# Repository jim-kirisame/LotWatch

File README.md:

# LotWatch

LotWatch是一个自制的蓝牙手表项目。它使用了nRF51822作为核心，mma8452为加速度计。

使用[nRF SDK V10.0](https://developer.nordicsemi.com/nRF5_SDK/nRF51_SDK_v10.x.x/nRF51_SDK_10.0.0_dc26b5e.zip)开发，并在Keil MDK v5下编译通过。

## 文件结构

- app-js：手机端应用程序，使用Cordova编写
- Application：手表的主程序部分
- Bootloader：手表的Bootloader，用于OTA
- Hardware：硬件设计
- Release：编译好的各个程序，可以直接使用。

其余事项见各文件夹下的说明。

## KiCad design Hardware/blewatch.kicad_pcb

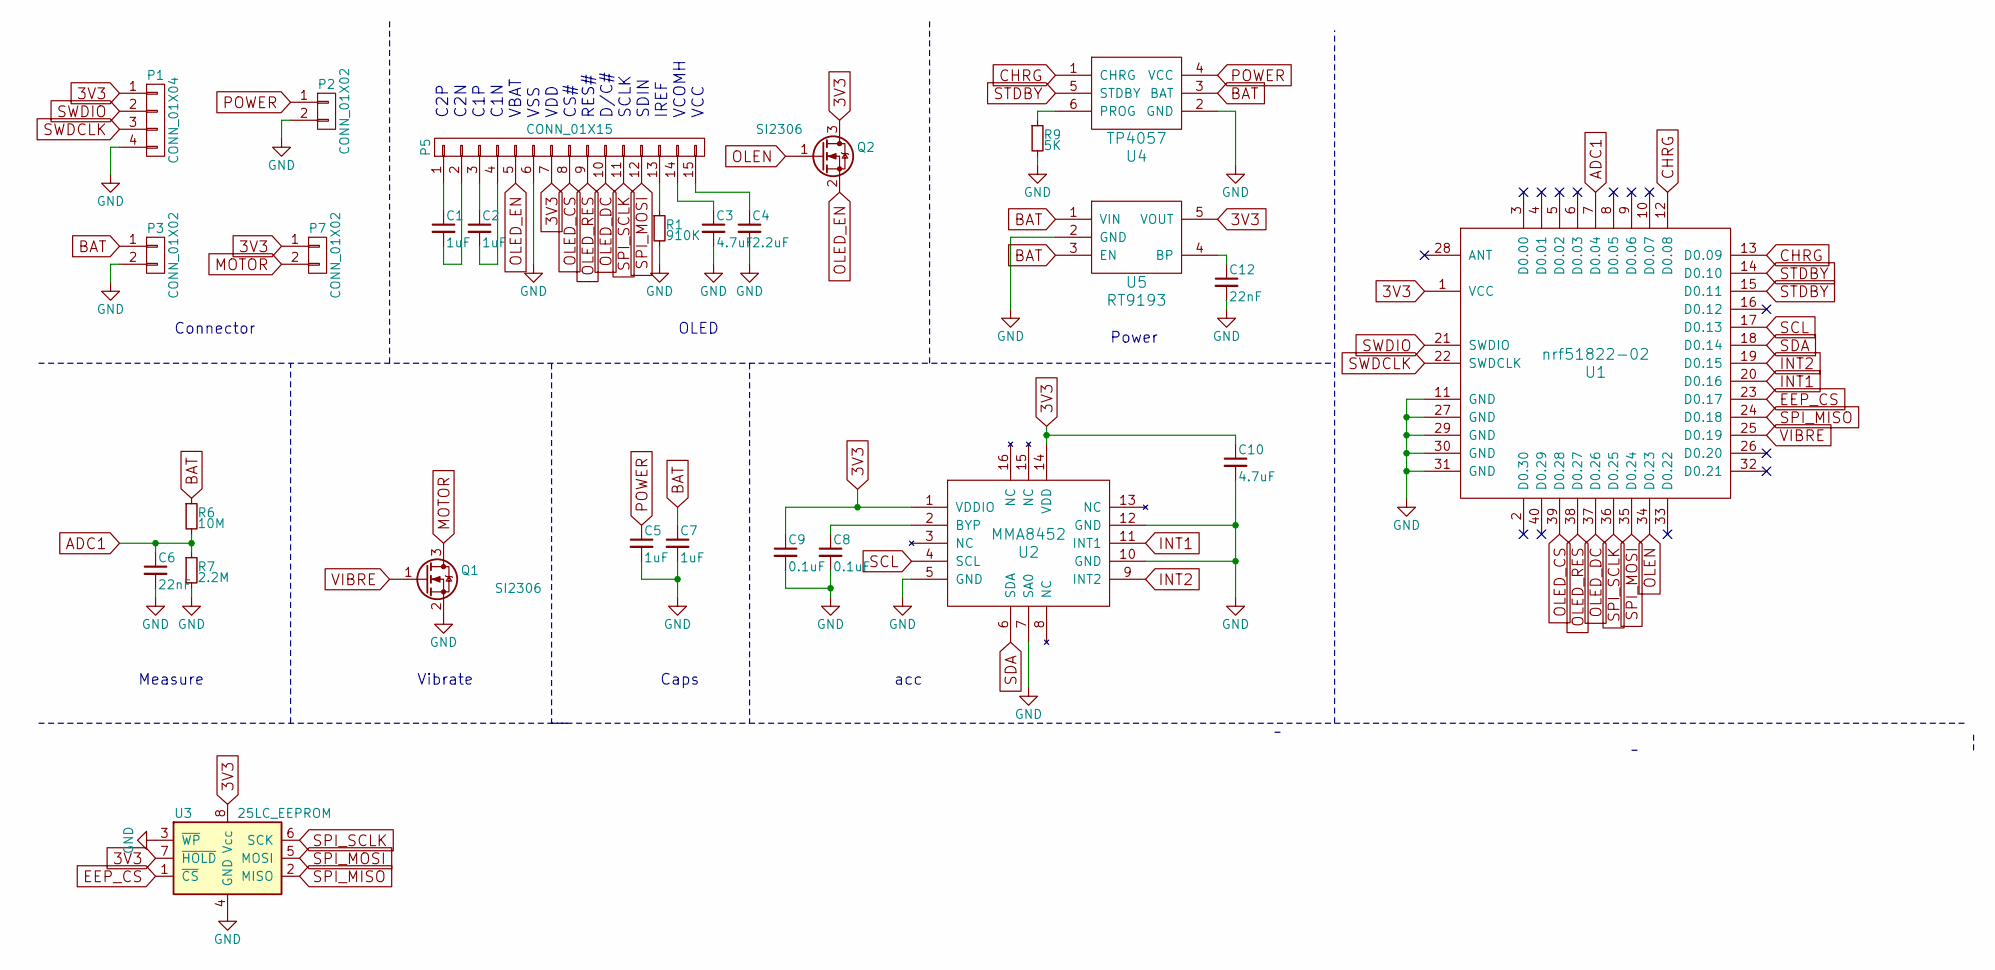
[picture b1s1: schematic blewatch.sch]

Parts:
C1, C2, C5, C7: 1uF; C_0805
C3, C10: 4.7uF; C_0805
C4: 2.2uF; C_0805
C6, C12: 22nF; C_0805
C8, C9: 0.1uF; C_0805
P1: CONN_01X04; SIP-4-1.27
P2, P3, P7: CONN_01X02; SIP-2-1.27
P5: CONN_01X15; OLED-15PIN
Q1, Q2: SI2306; SOT-23
R1: 910K; R_0805
R6: 10M; R_0805
R7: 2.2M; R_0805
R9: 5K; R_0805
U1: nrf51822-02; nRF51822-02
U2: MMA8452; QFN-16-1EP_3x3mm_Pitch0.5mm_SPEC
U3: 25LC_EEPROM; SOIC-8-N
U4: TP4057; SOT-23-6
U5: RT9193; SOT-23-5

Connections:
3V3: C9.1, C10.1, P1.1, P5.7, P7.1, Q2.3 (D), U1.1 (VCC), U2.1 (VDDIO), U2.14 (VDD), U3.7 (~HOLD), U3.8 (Vcc), U5.5 (VOUT)
ADC1: C6.1, R6.2, R7.1, U1.7 (D0.04)
BAT: C7.1, P3.1, R6.1, U4.3 (BAT), U5.1 (VIN), U5.3 (EN)
CHRG: U1.12 (D0.08), U1.13 (D0.09), U4.1 (CHRG)
EEP_CS: U1.23 (D0.17), U3.1 (~CS)
GND: C3.2, C4.2, C5.2, C6.2, C7.2, C8.2, C9.2, C10.2, C12.2, P1.4, P2.2, P3.2, P5.6, Q1.2 (S), R1.2, R7.2, R9.2, U1.11 (GND), U1.27 (GND), U1.29 (GND), U1.30 (GND), U1.31 (GND), U2.5 (GND), U2.7 (SA0), U2.10 (GND), U2.12 (GND), U3.3 (~WP), U3.4 (GND), U4.2 (GND), U5.2 (GND)
INT1: U1.20 (D0.16), U2.11 (INT1)
INT2: U1.19 (D0.15), U2.9 (INT2)
MOTOR: P7.2, Q1.3 (D)
unnamed: C1.1, P5.1
unnamed: C1.2, P5.2
unnamed: C2.1, P5.3
unnamed: C2.2, P5.4
unnamed: C3.1, P5.14
unnamed: C4.1, P5.15
unnamed: C8.1, U2.2 (BYP)
unnamed: C12.1, U5.4 (BP)
unnamed: P5.13, R1.1
unnamed: R9.1, U4.6 (PROG)
OLED_CS: P5.8, U1.39 (D0.28)
OLED_DC: P5.10, U1.37 (D0.26)
OLED_EN: P5.5, Q2.2 (S)
OLED_RES: P5.9, U1.38 (D0.27)
OLEN: Q2.1 (G), U1.34 (D0.23)
POWER: C5.1, P2.1, U4.4 (VCC)
SCL: U1.17 (D0.13), U2.4 (SCL)
SDA: U1.18 (D0.14), U2.6 (SDA)
SPI_MISO: U1.24 (D0.18), U3.2 (MISO)
SPI_MOSI: P5.12, U1.35 (D0.24), U3.5 (MOSI)
SPI_SCLK: P5.11, U1.36 (D0.25), U3.6 (SCK)
STDBY: U1.14 (D0.10), U1.15 (D0.11), U4.5 (STDBY)
SWDCLK: P1.3, U1.22 (SWDCLK)
SWDIO: P1.2, U1.21 (SWDIO)
VIBRE: Q1.1 (G), U1.25 (D0.19)

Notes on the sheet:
C2P C2N C1P C1N VBAT VSS VDD CS# RES# D/C# SCLK SDIN IREF VCOMH VCC
Connector
OLED
Power
Vibrate
acc
Measure
Caps

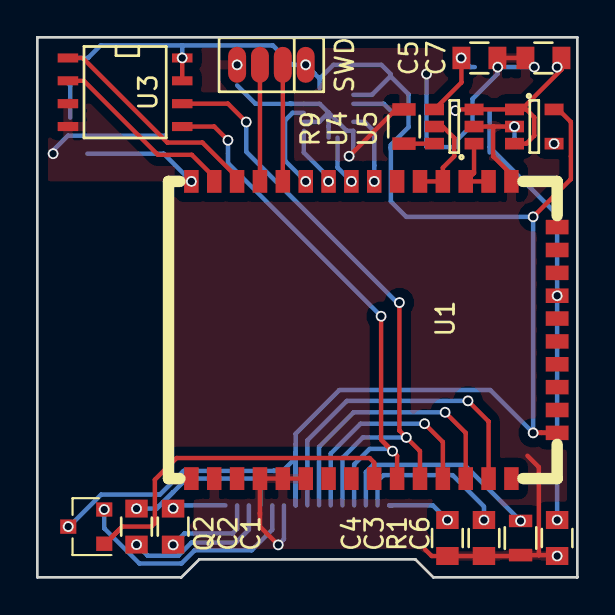
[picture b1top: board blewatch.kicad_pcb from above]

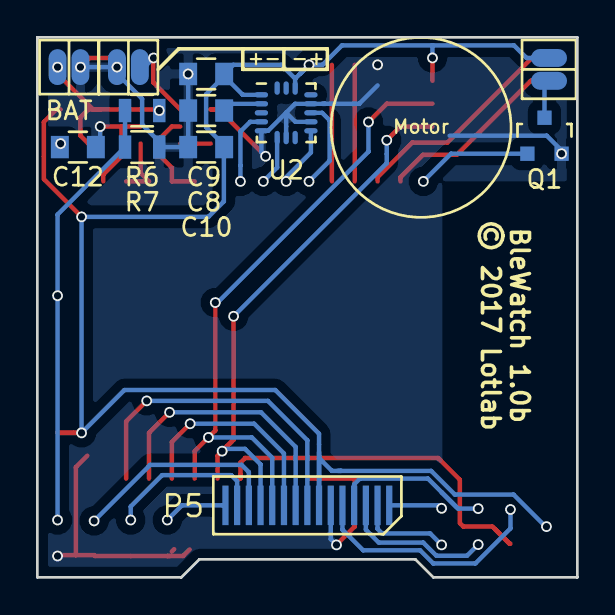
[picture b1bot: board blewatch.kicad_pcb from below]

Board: 2 copper layers, 30.0 x 30.0 mm, 27 parts (12 on the bottom side), 34 nets.

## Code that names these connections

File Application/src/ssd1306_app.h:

#ifndef _SSD1306_APP_
#define _SSD1306_APP_
#include <stdint.h>
#define SPI_RES 27
#define SPI_DC 26
#define SPI_SCLK 25
#define SPI_MOSI 24
#define SPI_MISO 18
#define OLED_EN 23
#define OLED_CS 28

#define SSD1306_SETCONTRAST 0x81
#define SSD1306_DISPLAYALLON_RESUME 0xA4
#define SSD1306_DISPLAYALLON 0xA5
#define SSD1306_NORMALDISPLAY 0xA6
#define SSD1306_INVERTDISPLAY 0xA7
#define SSD1306_DISPLAYOFF 0xAE
#define SSD1306_DISPLAYON 0xAF

#define SSD1306_SETDISPLAYOFFSET 0xD3
#define SSD1306_SETCOMPINS 0xDA

#define SSD1306_SETVCOMDETECT 0xDB

#define SSD1306_SETDISPLAYCLOCKDIV 0xD5
#define SSD1306_SETPRECHARGE 0xD9

#define SSD1306_SETMULTIPLEX 0xA8

#define SSD1306_SETLOWCOLUMN 0x00
#define SSD1306_SETHIGHCOLUMN 0x10

#define SSD1306_SETSTARTLINE 0x40

#define SSD1306_MEMORYMODE 0x20
#define SSD1306_COLUMNADDR 0x21
#define SSD1306_PAGEADDR   0x22

#define SSD1306_COMSCANINC 0xC0
#define SSD1306_COMSCANDEC 0xC8

#define SSD1306_SEGREMAP 0xA0

#define SSD1306_CHARGEPUMP 0x8D

#define SSD1306_EXTERNALVCC 0x1
#define SSD1306_SWITCHCAPVCC 0x2

// Scrolling #defines
#define SSD1306_ACTIVATE_SCROLL 0x2F
#define SSD1306_DEACTIVATE_SCROLL 0x2E
#define SSD1306_SET_VERTICAL_SCROLL_AREA 0xA3
#define SSD1306_RIGHT_HORIZONTAL_SCROLL 0x26
#define SSD1306_LEFT_HORIZONTAL_SCROLL 0x27
#define SSD1306_VERTICAL_AND_RIGHT_HORIZONTAL_SCROLL 0x29
#define SSD1306_VERTICAL_AND_LEFT_HORIZONTAL_SCROLL 0x2A

extern uint8_t buffer[];

void ssd1306_clearDisplay(void);
void ssd1306_display(void);
void ssd1306_stopScroll(void);
void ssd1306_startScrollDiagLeft(uint8_t start, uint8_t stop);
void ssd1306_startScrollDiagRight(uint8_t start, uint8_t stop);
void ssd1306_startScrollLeft(uint8_t start, uint8_t stop);
void ssd1306_startScrollRight(uint8_t start, uint8_t stop);
void ssd1306_invertDisplay(_Bool i);
void ssd1306_drawPixel(uint8_t x, uint8_t y, _Bool white);
void ssd1306_drawByte(uint8_t x, uint8_t y, uint8_t byte);
void ssd1306_init(void);
void ssd1306_write_data(uint8_t * data, uint32_t len);
void ssd1306_displayOff(void);
void ssd1306_displayOn(void);
void ssd1306_spi_init(void);
void ssd1306_spi_uninit(void);

#endif

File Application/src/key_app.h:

#ifndef _KEY_APP_H
#define _KEY_APP_H
#include <stdint.h>

//#define KEY_PIN 17
#define INT_PIN 16
#define INT2_PIN 15

#define CHRG_PIN_2 8
#define CHRG_PIN 9
#define STDBY_PIN 10
#define STDBY_PIN_2 11

extern _Bool charge_charging;
extern _Bool charge_fulled;

enum key_evt_type{
    TOUCH_KEY_EVENT=0xC0,
    TAP_ONCE_EVENT,
    TAP_TWICE_EVENT,
    WRIST_ROTATE_EVENT,
    CHARGING_EVENT,
    NOT_CHARGING_EVENT=0xc5,
    FULLED_EVENT,
    NOT_FULLED_EVENT,
    PASSCODE_DISP_EVENT,
    ALARM_DISP_EVENT,
    NORMAL_DISP_EVENT=0xca,
};

void key_init(void);
void key_set_evt_handler(void (*evt)(uint8_t));
void key_generate_evt(enum key_evt_type event);


#endif

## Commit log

2017-03-03 添加库文件
2017-03-03 添加工程文件
2017-03-03 设置工作环境
2017-03-03 添加RTE文件夹
2017-03-03 添加Bootloader相关文件
2017-03-03 修改Bootloader工程
2017-03-03 something
2017-03-06 [add] add DFU support
2017-03-06 [add] 增加电量服务
2017-03-08 添加oled驱动
2017-03-10 一大堆功能（
2017-03-11 bigger font
2017-03-11 add key and interrupt
2017-03-12 some changes
2017-03-13 USING APP_TIMER_APPSH_INIT INSTEAD OF APP_TIMER_INIT
2017-03-13 尝试添加串口/新的密码显示界面
2017-03-14 解决配对失败导致重启的问题
2017-03-17 创建通讯协议
2017-03-19 add android project
2017-03-19 add step_counter
2017-03-24 - 增加震动功能 - 增加闹铃功能
2017-03-26 更换16x字体，移动部分字体文件，增加再响限制次数，增加部分图标，增加电量图标，修正16x字体显示不正常的问题，微调事件判断逻辑
2017-03-26 增加配置和数据管理模块
2017-03-27 增加充电页面，补全通信协议，增加页面顺序配置，增加名称配置，
2017-03-30 wwww
2017-03-30 嗯……就这样吧
2017-04-02 先这样吧
2017-04-03 发送调试数据，动态关闭SPI，减少APP_TIMER，调整灵敏度，调整TIMER分频，增加看门狗，延长蓝牙发包间隔，减小蓝牙功率，改变供电方式，修改睡眠函数，关闭TIMER0，修正修改时间导致卡死的BUG，电量中值滤波，微调显示，删除示例闹铃 安卓一堆改动
2017-04-05 修改一点问题
2017-04-08 remove temper measurement, remove BAS service, fix adv start bug. low power of GPIOTE, reverse z-axis tap detection, disable UART, tweak some display page.
2017-04-14 优化SSD1306进入睡眠模式逻辑 修改8452采样率 优化充电显示逻辑 添加编译日期显示
2017-04-14 删除无用模块
2017-04-14 删除空文件夹
2017-05-04 修改Bootloader的原理
2017-05-05 add js-app
2017-05-05 基本能用系列
2017-05-08 修改Bootloader强制进入方式为短接TTL口 增加屏幕提示，删除震动提示
2017-05-10 加快屏幕绘制速度
2017-05-25 增加加速度打印功能
2017-05-29 不知道改了什么 反正提交就对了
2017-06-07 硬件布局更新
    - 移除百度计步算法
    - 增加自己写的计步算法
    - 修正充电显示
    - 替换加速度计DEBUG显示方案
2017-06-07 修改Bootloader进入方式和等待方式
2017-12-09 删除无用的老旧APP版本
2017-12-09 移动主要代码到new.html,微调部分样式
2017-12-09 微调部分数据结构和算法
2017-12-09 增加硬件部分
2017-12-09 添加说明文档等东西

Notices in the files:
Hardware/blewatch.kicad_pcb:
© 2017 Lotlab
